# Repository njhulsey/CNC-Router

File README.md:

# CNC-Router
CNC Router based off of the A4988 and ATmega2560

This board used the ATmega2560 to control 3 steppers, 4 servos, and manage 3 switches! Quite a lot to it! It also has a flex cable for an interface board to provide more user interaction. The board will an Oled, potentiometers and buttons. There's a barrel jack connector for the steppers power and an ftdi chip for serial communication. Got these made from PCBway. Been really happy with the finishes and the prices are pretty unbeatable.

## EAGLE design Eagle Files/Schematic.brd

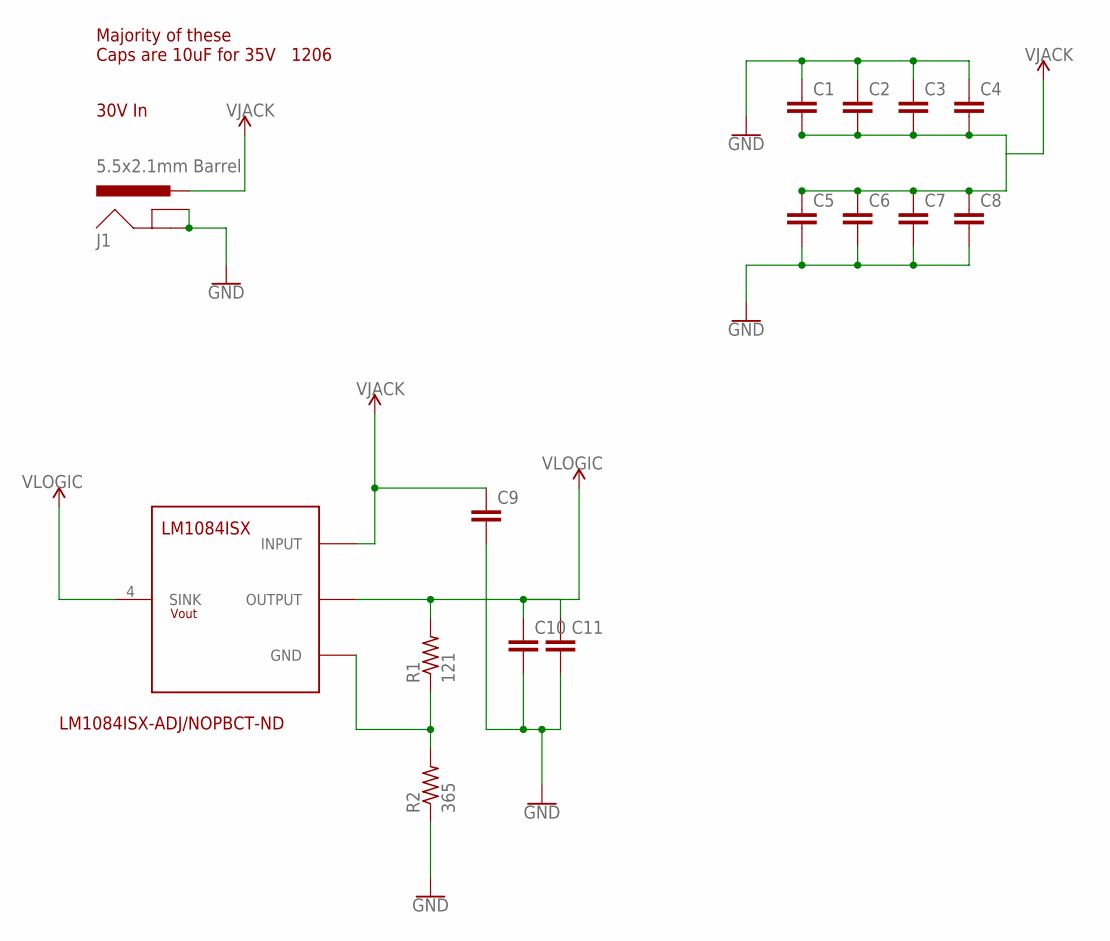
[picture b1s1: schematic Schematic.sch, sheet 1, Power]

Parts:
C1, C2, C3, C4, C5, C6, C7, C8, C9, C10, C11: C-EUC1206K; C1206K
J1: 5.5x2.1mm Barrel; POWER_JACK_SMD
R1: 121; R0805
R2: 365; R0805
U$2: LM1084ISX; TO254P1435X464-4N

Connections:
GND: C1.1, C2.1, C3.1, C4.1, C5.2, C6.2, C7.2, C8.2, C9.2, C10.2, C11.2, J1.GND (GNDBREAK), J1.P$4 (GND), R2.1; also elsewhere on the board
unnamed: R1.1, R2.2, U$2.1 (GND)
VJACK: C1.2, C2.2, C3.2, C4.2, C5.1, C6.1, C7.1, C8.1, C9.1, J1.VIN0 (PWR), U$2.3 (INPUT); also elsewhere on the board
VLOGIC: C10.1, C11.1, R1.2, U$2.2 (OUTPUT), U$2.4 (SINK); also elsewhere on the board

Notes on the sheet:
30V In
Majority of these Caps are 10uF for 35V
LM1084ISX-ADJ/NOPBCT-ND
1206

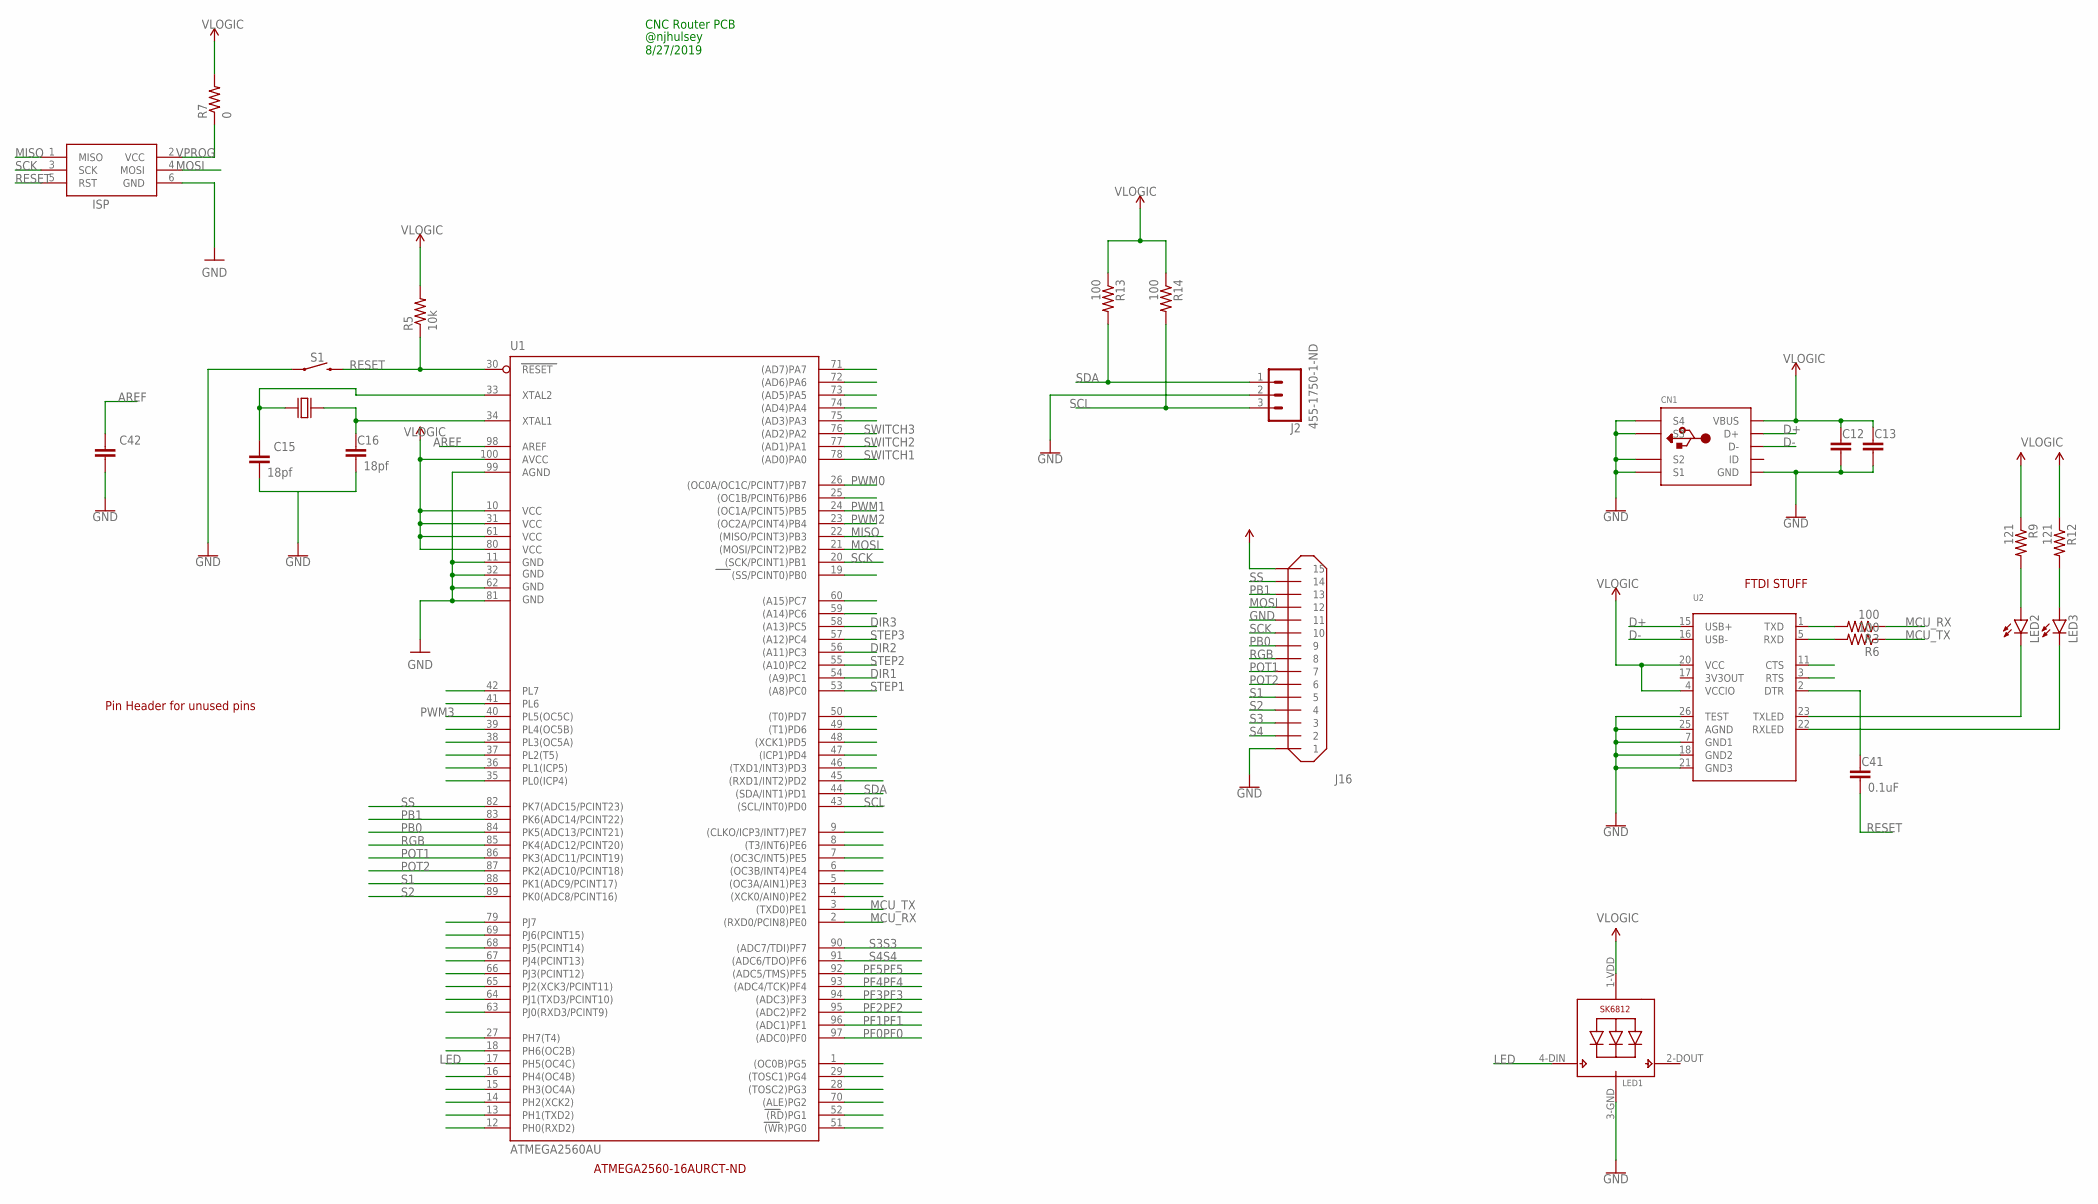
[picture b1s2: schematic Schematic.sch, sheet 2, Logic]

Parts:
C12, C13, C42: C-EUC0805; C0805
C15, C16: 18pf; C0805
C41: 0.1uF; C0805
CN1: USBMINIBLARGE; USB-MINIB_LARGER
ISP: AVRISP-6; AVRISP
J2: 455-1750-1-ND; 1X03
J16: MOLEX-15-FFC-VERT; MOLEX-VERT-FFC-15
LED1: SK6812_5050; LED5050
LED2, LED3: LEDCHIPLED_0805; CHIPLED_0805
R3, R6, R13, R14: 100; R0805
R5: 10k; R0805
R7: 0; R0805
R9, R12: 121; R0805
S1: MOMENTARY-SWITCH-SPST-SMD-5.2-REDUNDANT; TACTILE_SWITCH_SMD_5.2MM
U1: ATMEGA2560AU; TQFP100
U2: FT232RLSSOP28; SSOP28DB
U$1: CRYSTAL-SMD-HC-49US; CRYSTAL_SMD_HC-49/US

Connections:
3V3OUT: U2.17 (3V3OUT)
AREF: C42.1, U1.98 (AREF)
D+: CN1.D+, U2.15 (USB+)
D-: CN1.D-, U2.16 (USB-)
DIR1: U1.54 ((A9)PC1); also elsewhere on the board
DIR2: U1.56 ((A11)PC3); also elsewhere on the board
DIR3: U1.58 ((A13)PC5); also elsewhere on the board
GND: C12.2, C13.2, C15.2, C16.2, C42.2, CN1.GND, CN1.GND1 (S1), CN1.GND2 (S2), CN1.GND3 (S3), CN1.GND4 (S4), ISP.6 (GND), J2.2, J16.P$1 (1), J16.P$2 (1), J16.P$21 (11), J16.P$22 (11), LED1.3-GND (GND), S1.1, S1.2 (1), U1.11 (GND), U1.32 (GND1), U1.62 (GND2), U1.81 (GND3), U1.99 (AGND), U2.7 (GND1), U2.18 (GND2), U2.21 (GND3), U2.25 (AGND), U2.26 (TEST); also elsewhere on the board
LED: LED1.4-DIN (DI), U1.17 (PH5(OC4C))
MCU_RX: R3.1, U1.2 ((RXD0/PCIN8)PE0)
MCU_TX: R6.1, U1.3 ((TXD0)PE1)
MISO: ISP.1 (MISO), U1.22 ((MISO/PCINT3)PB3)
MOSI: ISP.4 (MOSI), J16.P$23 (12), J16.P$24 (12), U1.21 ((MOSI/PCINT2)PB2)
unnamed: LED2.A, R9.2
unnamed: LED3.A, R12.2
unnamed: R3.2, U2.1 (TXD)
unnamed: R6.2, U2.5 (RXD)
unnamed: C41.1, U2.2 (DTR)
unnamed: LED2.C, U2.23 (TXLED)
unnamed: LED3.C, U2.22 (RXLED)
unnamed: C15.1, U1.33 (XTAL2), U$1.P$2
unnamed: C16.1, U1.34 (XTAL1), U$1.P$1
PB0: J16.P$17 (9), J16.P$18 (9), U1.84 (PK5(ADC13/PCINT21))
PB1: J16.P$25 (13), J16.P$26 (13), U1.83 (PK6(ADC14/PCINT22))
PF0: U1.97 ((ADC0)PF0)
PF1: U1.96 ((ADC1)PF1)
PF2: U1.95 ((ADC2)PF2)
PF3: U1.94 ((ADC3)PF3)
PF4: U1.93 ((ADC4/TCK)PF4)
PF5: U1.92 ((ADC5/TMS)PF5)
POT1: J16.P$13 (7), J16.P$14 (7), U1.86 (PK3(ADC11/PCINT19))
POT2: J16.P$11 (6), J16.P$12 (6), U1.87 (PK2(ADC10/PCINT18))
PWM0: U1.26 ((OC0A/OC1C/PCINT7)PB7); also elsewhere on the board
PWM1: U1.24 ((OC1A/PCINT5)PB5); also elsewhere on the board
PWM2: U1.23 ((OC2A/PCINT4)PB4); also elsewhere on the board
PWM3: U1.40 (PL5(OC5C)); also elsewhere on the board
RESET: C41.2, ISP.5 (RST), R5.1, S1.3 (2), S1.4 (2), U1.30 (RESET)
RGB: J16.P$15 (8), J16.P$16 (8), U1.85 (PK4(ADC12/PCINT20))
S1: J16.P$9 (5), J16.P$10 (5), U1.88 (PK1(ADC9/PCINT17))
S2: J16.P$7 (4), J16.P$8 (4), U1.89 (PK0(ADC8/PCINT16))
S3: J16.P$5 (3), J16.P$6 (3), U1.90 ((ADC7/TDI)PF7)
S4: J16.P$3 (2), J16.P$4 (2), U1.91 ((ADC6/TDO)PF6)
SCK: ISP.3 (SCK), J16.P$19 (10), J16.P$20 (10), U1.20 ((SCK/PCINT1)PB1)
SCL: J2.3, R14.2, U1.43 ((SCL/INT0)PD0)
SDA: J2.1, R13.2, U1.44 ((SDA/INT1)PD1)
SS: J16.P$27 (14), J16.P$28 (14), U1.82 (PK7(ADC15/PCINT23))
STEP1: U1.53 ((A8)PC0); also elsewhere on the board
STEP2: U1.55 ((A10)PC2); also elsewhere on the board
STEP3: U1.57 ((A12)PC4); also elsewhere on the board
SWITCH1: U1.78 ((AD0)PA0); also elsewhere on the board
SWITCH2: U1.77 ((AD1)PA1); also elsewhere on the board
SWITCH3: U1.76 ((AD2)PA2); also elsewhere on the board
VCC: J16.P$29 (15), J16.P$30 (15)
VLOGIC: C12.1, C13.1, CN1.VBUS, LED1.1-VDD (VDD), R5.2, R7.2, R9.1, R12.1, R13.1, R14.1, U1.10 (VCC), U1.31 (VCC1), U1.61 (VCC2), U1.80 (VCC3), U1.100 (AVCC), U2.4 (VCCIO), U2.20 (VCC); also elsewhere on the board
VPROG: ISP.2 (VCC), R7.1

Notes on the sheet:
ATMEGA2560-16AURCT-ND
FTDI STUFF
Pin Header for unused pins
@njhulsey 8/27/2019
CNC Router PCB

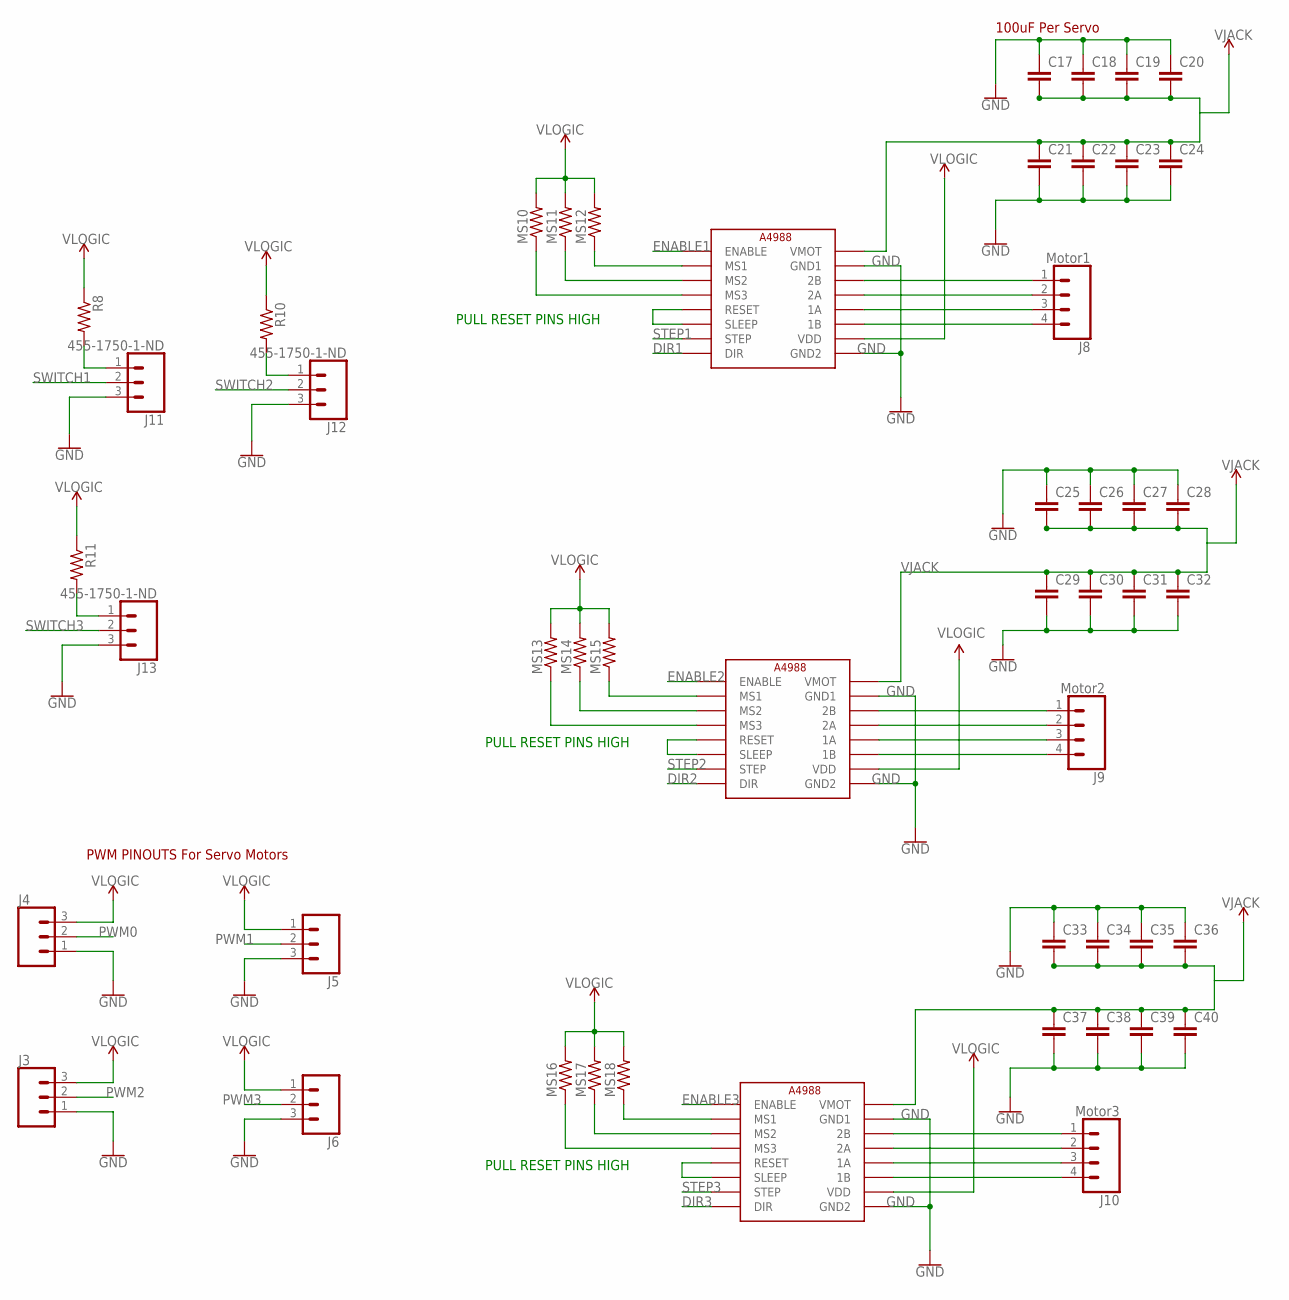
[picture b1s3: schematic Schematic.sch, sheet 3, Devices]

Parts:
C17, C18, C19, C20, C21, C22, C23, C24, C25, C26, C27, C28, C29, C30, C31, C32, C33, C34, C35, C36, C37, C38, C39, C40: C-EUC1206K; C1206K
DRVER_4, DRVER_5, DRVER_6: Driver1; A4988
J3, J4, J5, J6, J11, J12, J13: 455-1750-1-ND; 1X03
J8: Motor1; 1X04
J9: Motor2; 1X04
J10: Motor3; 1X04
MS10, MS11, MS12, MS13, MS14, MS15, MS16, MS17, MS18: R-US_R0805; R0805
R8, R10, R11: R-US_R0805; R0805

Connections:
DIR1: DRVER_4.P$9 (DIR); also elsewhere on the board
DIR2: DRVER_5.P$9 (DIR); also elsewhere on the board
DIR3: DRVER_6.P$9 (DIR); also elsewhere on the board
ENABLE1: DRVER_4.P$16 (ENABLE)
ENABLE2: DRVER_5.P$16 (ENABLE)
ENABLE3: DRVER_6.P$16 (ENABLE)
GND: C17.1, C18.1, C19.1, C20.1, C21.2, C22.2, C23.2, C24.2, C25.1, C26.1, C27.1, C28.1, C29.2, C30.2, C31.2, C32.2, C33.1, C34.1, C35.1, C36.1, C37.2, C38.2, C39.2, C40.2, DRVER_4.P$1 (GND2), DRVER_4.P$7 (GND1), DRVER_5.P$1 (GND2), DRVER_5.P$7 (GND1), DRVER_6.P$1 (GND2), DRVER_6.P$7 (GND1), J3.1, J4.1, J5.3, J6.3, J11.3, J12.3, J13.3; also elsewhere on the board
unnamed: J11.1, R8.2
unnamed: J12.1, R10.2
unnamed: J13.1, R11.2
unnamed: DRVER_4.P$13 (MS3), MS10.1
unnamed: DRVER_4.P$14 (MS2), MS11.1
unnamed: DRVER_4.P$15 (MS1), MS12.1
unnamed: DRVER_4.P$3 (1B), J8.4
unnamed: DRVER_4.P$4 (1A), J8.3
unnamed: DRVER_4.P$5 (2A), J8.2
unnamed: DRVER_4.P$6 (2B), J8.1
unnamed: DRVER_6.P$13 (MS3), MS16.1
unnamed: DRVER_6.P$14 (MS2), MS17.1
unnamed: DRVER_6.P$15 (MS1), MS18.1
unnamed: DRVER_6.P$6 (2B), J10.1
unnamed: DRVER_6.P$5 (2A), J10.2
unnamed: DRVER_6.P$4 (1A), J10.3
unnamed: DRVER_6.P$3 (1B), J10.4
unnamed: DRVER_5.P$15 (MS1), MS15.1
unnamed: DRVER_5.P$14 (MS2), MS14.1
unnamed: DRVER_5.P$13 (MS3), MS13.1
unnamed: DRVER_5.P$6 (2B), J9.1
unnamed: DRVER_5.P$5 (2A), J9.2
unnamed: DRVER_5.P$4 (1A), J9.3
unnamed: DRVER_5.P$3 (1B), J9.4
PWM0: J4.2; also elsewhere on the board
PWM1: J5.2; also elsewhere on the board
PWM2: J3.2; also elsewhere on the board
PWM3: J6.2; also elsewhere on the board
SLEEP3: DRVER_4.P$11 (SLEEP), DRVER_4.P$12 (RESET)
SLEEP4: DRVER_5.P$11 (SLEEP), DRVER_5.P$12 (RESET)
SLEEP5: DRVER_6.P$11 (SLEEP), DRVER_6.P$12 (RESET)
STEP1: DRVER_4.P$10 (STEP); also elsewhere on the board
STEP2: DRVER_5.P$10 (STEP); also elsewhere on the board
STEP3: DRVER_6.P$10 (STEP); also elsewhere on the board
SWITCH1: J11.2; also elsewhere on the board
SWITCH2: J12.2; also elsewhere on the board
SWITCH3: J13.2; also elsewhere on the board
VJACK: C17.2, C18.2, C19.2, C20.2, C21.1, C22.1, C23.1, C24.1, C25.2, C26.2, C27.2, C28.2, C29.1, C30.1, C31.1, C32.1, C33.2, C34.2, C35.2, C36.2, C37.1, C38.1, C39.1, C40.1, DRVER_4.P$8 (VMOT), DRVER_5.P$8 (VMOT), DRVER_6.P$8 (VMOT); also elsewhere on the board
VLOGIC: DRVER_4.P$2 (VDD), DRVER_5.P$2 (VDD), DRVER_6.P$2 (VDD), J3.3, J4.3, J5.1, J6.1, MS10.2, MS11.2, MS12.2, MS13.2, MS14.2, MS15.2, MS16.2, MS17.2, MS18.2, R8.1, R10.1, R11.1; also elsewhere on the board

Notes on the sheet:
100uF Per Servo
PWM PINOUTS For Servo Motors
PULL RESET PINS HIGH

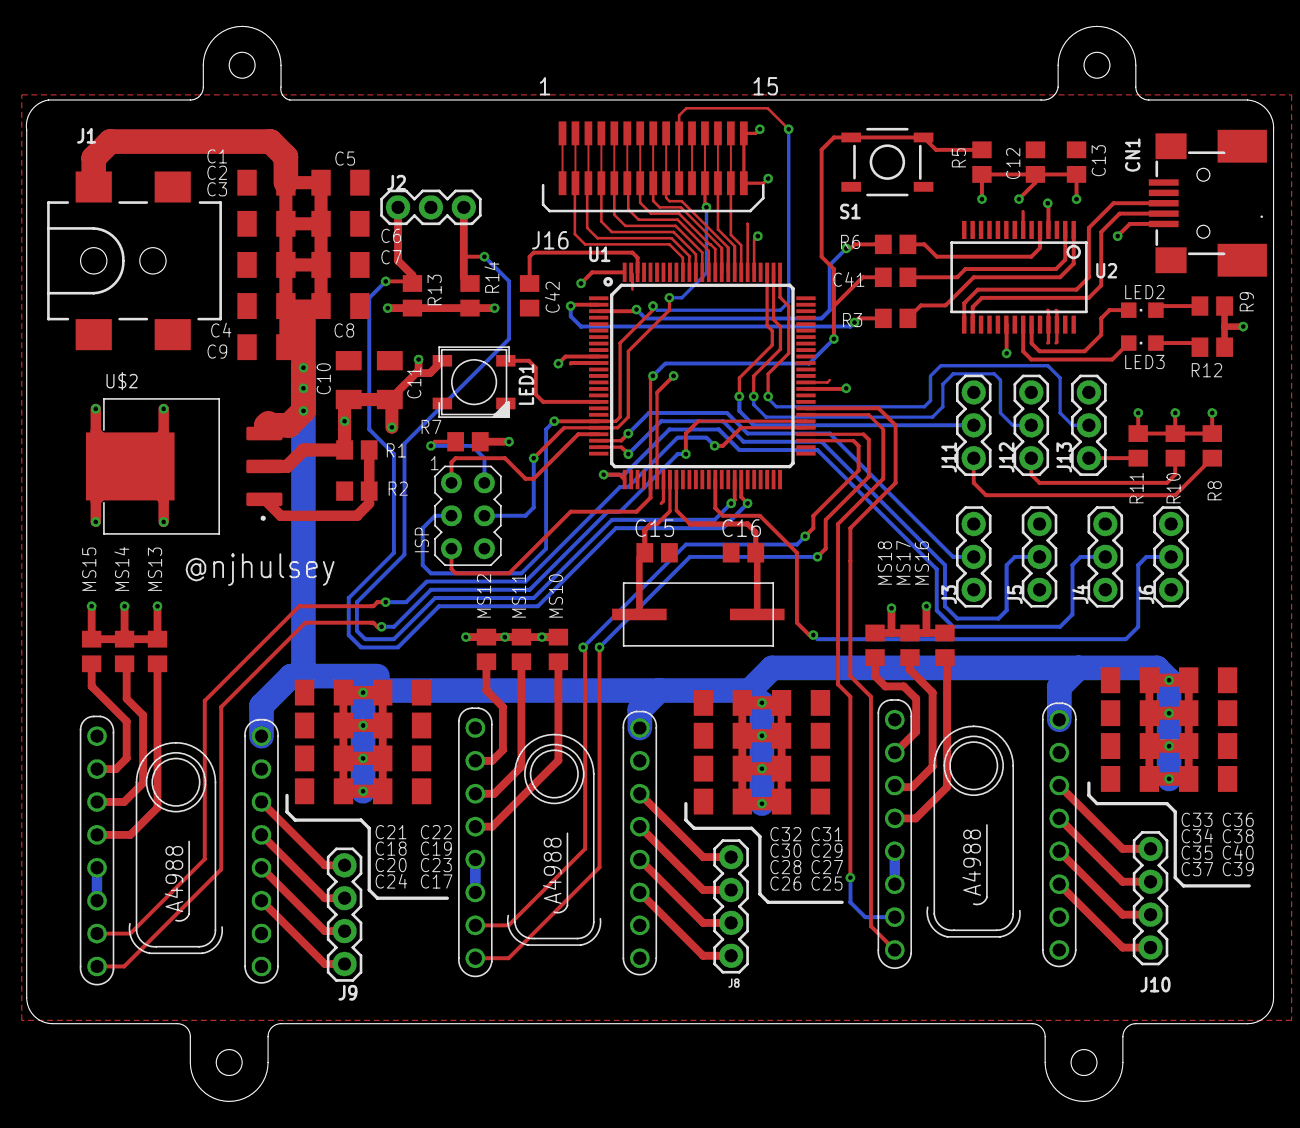
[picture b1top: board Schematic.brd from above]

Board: 2 copper layers, 96.3 x 83.0 mm, 89 parts (0 on the bottom side), 77 nets.

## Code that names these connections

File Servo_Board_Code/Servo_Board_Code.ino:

/**
 * This is simple test code for my CNC Router PCB
 * You can find out more at www.github.com/njhulsey
 * 
 * 
 * Nick Hulsey (@njhulsey)
 * 8/27/2019
 */


#include <Adafruit_NeoPixel.h>

#define DIR1                 36
#define STEP1                37

#define DIR2                 34
#define STEP2                35

#define DIR3                 32
#define STEP3                33

#define NEO_PIXEL_PIN        8 
Adafruit_NeoPixel pixels(1, NEO_PIXEL_PIN, NEO_GRB + NEO_KHZ800);

void setup() {

  pixels.begin(); // INITIALIZE NeoPixel strip object (REQUIRED)
  pixels.setBrightness(20);
  ledColor(0xFF00BF);

  Serial.begin(115200);
  ledColor(0x00DFBF);
  

  pinMode(DIR1,OUTPUT);
  pinMode(STEP1,OUTPUT);

  pinMode(DIR2,OUTPUT);
  pinMode(STEP2,OUTPUT);
  
  pinMode(DIR3,OUTPUT);
  pinMode(STEP3,OUTPUT);


}

void loop() {

  delay(1000);
  Serial.write("Turning motor 1 for 500 millisec\n");
 
  digitalWrite(DIR1,HIGH); // Enables the motor to move in a particular direction
  digitalWrite(DIR2,LOW);
  // Makes 200 pulses for making one full cycle rotation
  for(int x = 0; x < 800; x++) {
    digitalWrite(STEP1,HIGH); 
    digitalWrite(STEP2,HIGH);
    delayMicroseconds(500); 
    digitalWrite(STEP1,LOW); 
    digitalWrite(STEP2,LOW);
    delayMicroseconds(500); 
  }
  delay(1000); // One second delay
  
}


void ledColor(uint32_t color){
  pixels.setPixelColor(0, color);
  pixels.show();   // Send the updated pixel colors to the hardware.
}

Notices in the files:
parts and their libraries:
SparkFun-Connectors: Licensing: Creative Commons ShareAlike 4.0 International - https://creativecommons.org/licenses/by-sa/4.0
microbuilder: This work is placed in the public domain, and may be freely used for commercial and non-commercial work with the following conditions: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
